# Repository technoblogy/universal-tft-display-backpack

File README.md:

# Universal TFT Display Backpack
Eagle files for a microcontroller board, based on an ATtiny414, that can accommodate a range of different Adafruit and AliExpress colour TFT displays.

See <http://www.technoblogy.com/show?3JCM>.

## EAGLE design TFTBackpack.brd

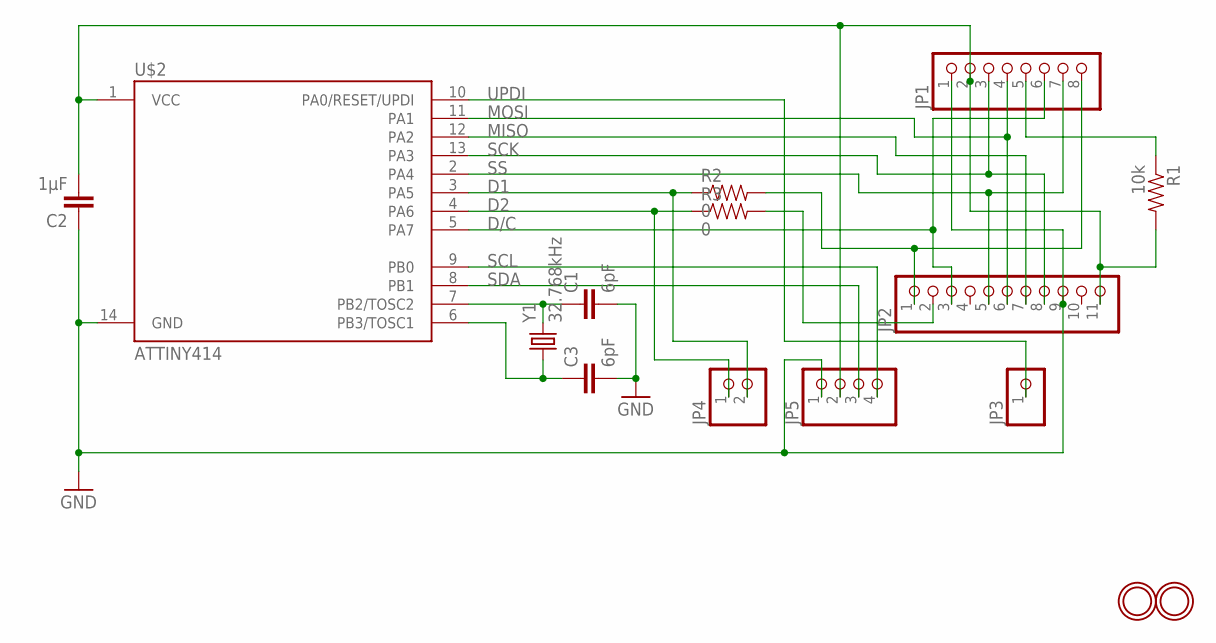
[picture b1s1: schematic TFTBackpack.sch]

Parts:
C1, C3: 6pF; 0805
C2: 1µF; 0805
JP1: HEADER-1X8ROUND; 1X08_ROUND
JP2: HEADER-1X11; 1X11_ROUND
JP3: HEADER-1X1ROUND; 1X01_ROUND
JP4: HEADER-1X2ROUND; 1X02_ROUND
JP5: HEADER-1X4ROUND; 1X04_ROUND
R1: 10k; 0805
R2, R3: 0; 0805
U$1, U$9: MOUNTINGHOLE2.5; MOUNTINGHOLE_2.5_PLATED
U$2: ATTINY414; SO14
Y1: 32.768kHz; CRYSTAL-SMD-3.2X1.5MM

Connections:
BL: JP1.8, JP2.1, R2.2
D1: JP4.2, R2.1, U$2.3 (PA5)
D2: JP4.1, R3.1, U$2.4 (PA6)
D/C: JP1.6, JP2.3, U$2.5 (PA7)
GND: C1.2, C2.1, C3.2, JP1.1, JP2.9, JP5.1, U$2.14 (GND)
MISO: JP2.7, U$2.12 (PA2)
MOSI: JP1.4, JP2.6, U$2.11 (PA1)
unnamed: C1.1, U$2.7 (PB2/TOSC2), Y1.P$2 (2)
unnamed: C3.1, U$2.6 (PB3/TOSC1), Y1.P$1 (1)
unnamed: JP1.5, R1.1
unnamed: JP2.2, R3.2
SCK: JP1.3, JP2.8, U$2.13 (PA3)
SCL: JP5.4, U$2.9 (PB0)
SDA: JP5.3, U$2.8 (PB1)
SS: JP1.7, JP2.5, U$2.2 (PA4)
UPDI: JP3.1, U$2.10 (PA0/RESET/UPDI)
VCC: C2.2, JP1.2, JP2.11, JP5.2, R1.2, U$2.1 (VCC)

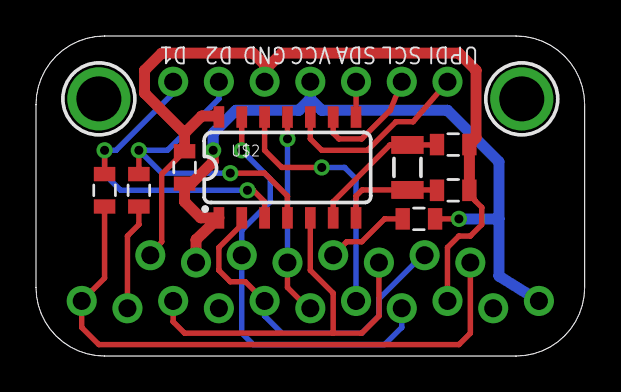
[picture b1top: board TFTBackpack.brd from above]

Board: 2 copper layers, 30.5 x 17.8 mm, 15 parts (0 on the bottom side), 17 nets.

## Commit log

2022-05-11 Version 1 - 11th May 2022

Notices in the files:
parts and their libraries:
microbuilder: This work is placed in the public domain, and may be freely used for commercial and non-commercial work with the following conditions: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
SparkFun-Capacitors: Licensing: CC v3.0 Share-Alike You are welcome to use this library for commercial purposes.
